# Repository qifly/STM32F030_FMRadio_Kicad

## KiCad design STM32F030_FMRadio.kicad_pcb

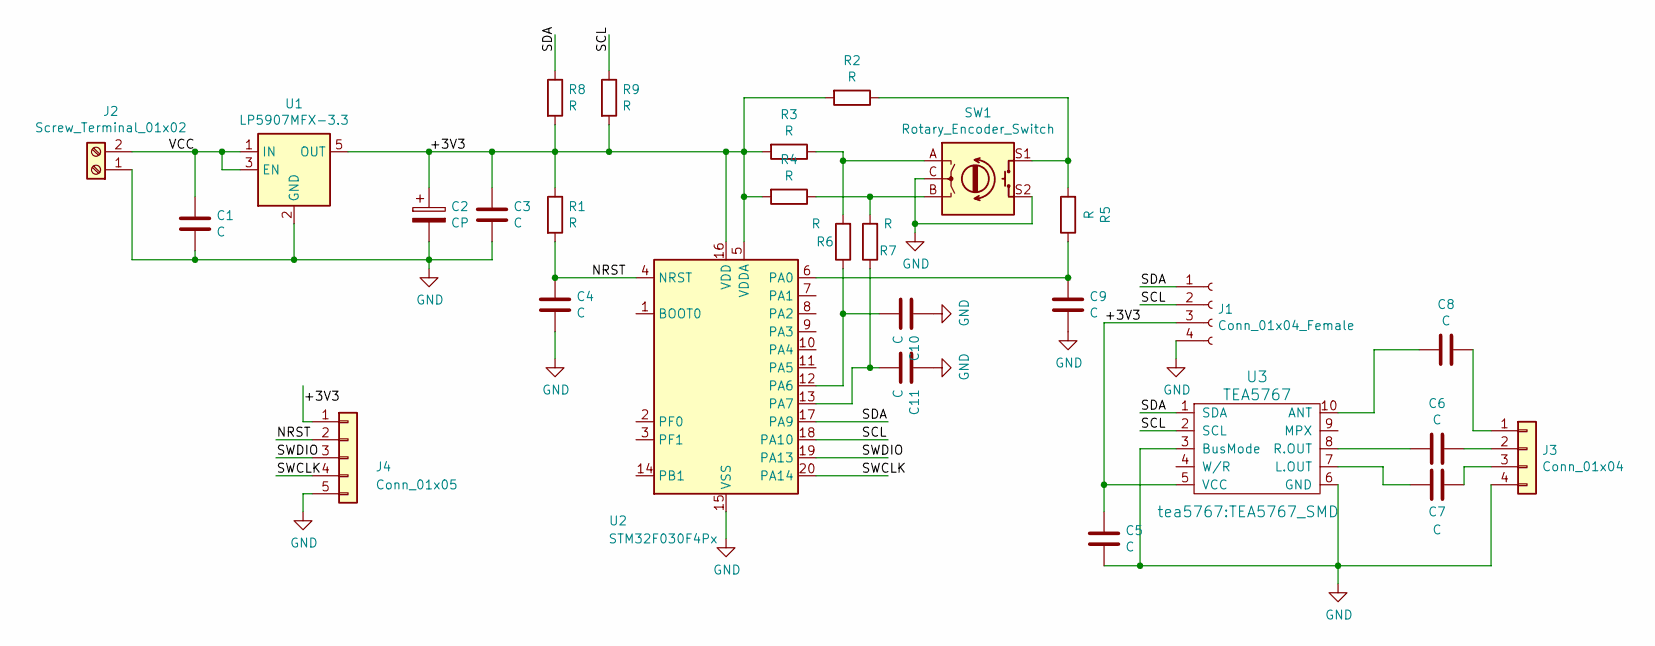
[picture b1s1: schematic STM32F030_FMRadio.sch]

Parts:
C1, C3, C4, C5, C6, C7, C8, C9, C10, C11: C; C_0805_2012Metric
C2: CP; CP_EIA-2012-15_AVX-P
J1: Conn_01x04_Female; SSD1306-0.91-OLED-4pin-128x32
J2: Screw_Terminal_01x02; PinHeader_1x02_P2.54mm_Vertical
J3: Conn_01x04; PinHeader_1x04_P2.54mm_Vertical
J4: Conn_01x05; PinHeader_1x05_P2.54mm_Vertical
R1, R2, R3, R4, R5, R6, R7, R8, R9: R; R_0805_2012Metric
SW1: Rotary_Encoder_Switch; RotaryEncoder_Alps_EC11E-Switch_Vertical_H20mm
U1: LP5907MFX-3.3; SOT-23-5
U2: STM32F030F4Px; TSSOP-20_4.4x6.5mm_P0.65mm
U3: TEA5767; TEA5767_SMD

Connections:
/+3V3: C2.1, C3.1, C5.1, J1.3, J4.1, R1.1, R2.2, R3.2, R4.2, R8.2, R9.2, U1.5 (OUT), U2.5 (VDDA), U2.16 (VDD), U3.5 (VCC)
/NRST: C4.1, J4.2, R1.2, U2.4 (NRST)
/SCL: J1.2, R9.1, U2.18 (PA10), U3.2 (SCL)
/SDA: J1.1, R8.1, U2.17 (PA9), U3.1 (SDA)
/SWCLK: J4.4, U2.20 (PA14)
/SWDIO: J4.3, U2.19 (PA13)
/VCC: C1.1, J2.2, U1.1 (IN), U1.3 (EN)
GND: C1.2, C2.2, C3.2, C4.2, C5.2, C9.2, C10.1, C11.1, J1.4, J2.1, J3.4, J4.5, SW1.C, SW1.S2, U1.2 (GND), U1.4 (NC), U2.15 (VSS), U3.3 (BusMode), U3.6 (GND)
unnamed: C6.1, J3.2
unnamed: C6.2, U3.8 (R.OUT)
unnamed: C7.1, J3.3
unnamed: C7.2, U3.7 (L.OUT)
unnamed: C8.1, J3.1
unnamed: C8.2, U3.10 (ANT)
unnamed: C9.1, R5.1, U2.6 (PA0)
unnamed: C10.2, R6.1, U2.12 (PA6)
unnamed: C11.2, R7.1, U2.13 (PA7)
unnamed: R2.1, R5.2, SW1.S1
unnamed: R3.1, R6.2, SW1.A
unnamed: R4.1, R7.2, SW1.B

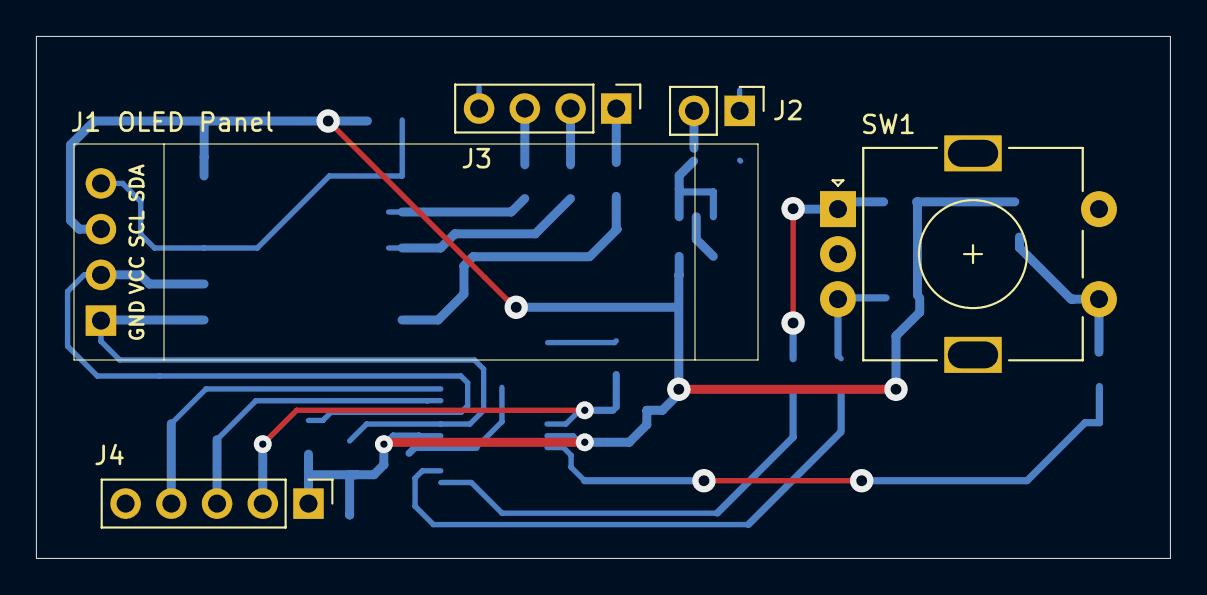
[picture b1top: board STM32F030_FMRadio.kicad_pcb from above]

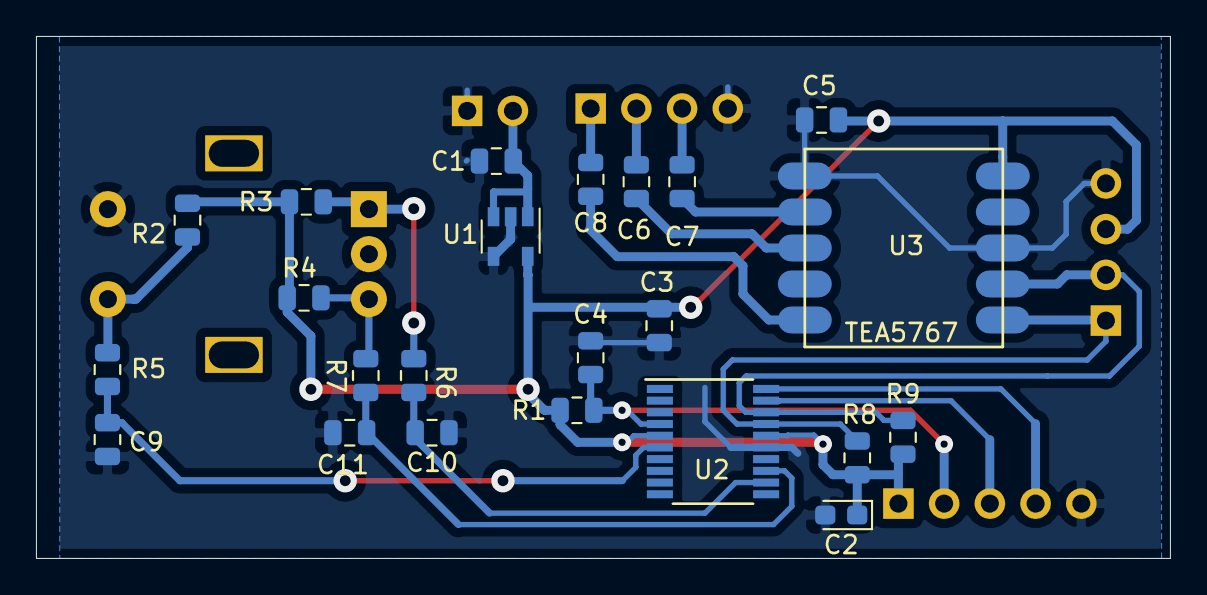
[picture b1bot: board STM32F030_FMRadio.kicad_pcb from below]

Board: 2 copper layers, 63.0 x 29.0 mm, 28 parts (23 on the bottom side), 20 nets.

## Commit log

2020-01-30 + pull_Up encoder, разведена ПП
2020-01-30 малкие правки разводки
2020-01-31 добавлена подтяжка на I2C, перетрассировка
2020-01-31 увеличина толщина дорожек
